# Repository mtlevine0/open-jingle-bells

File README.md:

# Open Jingle Bells

An ESP32-based replacement for the "Ye Merrie Minstrel Caroling Christmas Bells" original ROM cartridge featuring wireless synchronization.  Every unit carries the same song library, and any number of units on the same Wi-Fi network play in unison, creating a choir of christmas bells.

## Overview

This project provides open-source firmware and hardware designs to replace the original ROM cartridge in Ye Merrie Minstrel handheld bell units. Using ESP-NOW wireless communication, multiple sets of bells can be synchronized to play together in a choir.  The PCB is meant to be a direct drop-in replacement to the original ROM cartridge, no modifications of the device is required.  I reccomend a power adapter with a larger current capacity than the original 200mA to compensate for the extra power comsumption of the ESP32.

I used [OSH Park](https://oshpark.com) to manufacture the PCBs.  

## Project Structure

```
├── firmware/           # Bell-unit firmware (Arduino sketch): Wi-Fi control page, songs, UDP group sync
│   └── rom-dumper/     # Firmware for dumping ROM contents over a serial connection
├── hardware/
│   └── open-jingle-bells-module/  # KiCad project: bell-unit board
├── tools/              # Python package: song library (roms/), new songs (songs/), song and bell tools, sync monitor
└── docs/
```

## Hardware

The custom PCB is designed in KiCad and interfaces with the original bell unit via a 24-pin edge card connector, replacing the ROM cartridge.

## Demo

[View operation video](https://youtube.com/shorts/tzY3T9JohGE?feature=share)

## Firmware

### Bell unit
Each bell unit runs the Open Jingle Bells firmware. It plays its compiled-in song library by driving the 12-bit parallel data bus to the bell's solenoids. A phone sets it up and controls it through a web page, and units on the same network keep a shared clock over UDP so they play together. It also takes strikes over USB serial, for developing songs. See `firmware/README.md`.

### Rom Dumper
The original ROM contains copyrighted material.  I don't have permission to share the contents.  You can acquire your own ROM cartridge and dump the ROM using the Arduino program provided.

## Requirements

- ESP32 development boards
- Arduino IDE with ESP32 board support
- KiCad (for hardware modifications)

## License

This project is licensed under the MIT License - see the [LICENSE](LICENSE) file for details.

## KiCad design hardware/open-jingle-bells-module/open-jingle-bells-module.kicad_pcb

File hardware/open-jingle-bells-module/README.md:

# open-jingle-bells-module

ESP32-S3 receiver board that plugs onto the bell unit's card edge (J2, EDAC 395-024-559-212).

## Rev 2 (branch `choir-v2`)

### EN fix

On rev 1, R1 (10k) ran from EN to C3, and C3 went to GND. EN had no pull-up to +3.3V.
Rev 2 wires the standard Espressif RC:

- R1 10k: +3.3V to EN
- C3 1uF: EN to GND

### J2 moved to the bottom side

The socket now hangs under the board. Its slot, mounting holes and pin rows sit in the
same X/Y positions as rev 1, so the card enters from the same side. The board now sits
at a different height relative to the card, so check the enclosure stack-up.

Mounting the socket upside down turns it 180 degrees about the insertion axis. The
contact that touches card finger *n* is now socket pin **25 − n**. The schematic has been
re-pinned to match, so every net still reaches the same finger on the bell card:

| Signal | Rev 1 J2 pin | Rev 2 J2 pin |
|--------|-------------:|-------------:|
| Bell_1 / Bell_7  | 3 / 4   | 22 / 21 |
| Bell_2 / Bell_8  | 5 / 6   | 20 / 19 |
| Bell_3 / Bell_9  | 7 / 8   | 18 / 17 |
| GND / VCC        | 9 / 10  | 16 / 15 |
| Bell_4 / Bell_10 | 19 / 20 | 6 / 5   |
| Bell_5 / Bell_11 | 21 / 22 | 4 / 3   |
| Bell_6 / Bell_12 | 23 / 24 | 2 / 1   |

No firmware change is needed, because the ESP32 GPIO for each bell is unchanged.

J2 uses `card_edge_395024559212_noMH`, the rev 1 footprint without its two mounting
holes. The socket's mounting ears hang off the board edge and the socket is held by its
24 solder pins. Because the schematic symbol still has its MH1/MH2 pins (no-connect),
the parity check warns that pins 25 and 26 have no pad.

### Smaller outline

The board is 53.7–80.5 × 61–98 mm (26.8 × 37 mm), down from 35 × 55 mm in rev 1 and
26.8 × 47 mm in the first rev 2 layout. What sets the limits:

- left edge: 0.5 mm outside the copper of J2's outer pin row
- top edge: the base of the module's antenna; the antenna hangs off the board
- bottom edge: J2's lowest pins (y 94.55) and the stack of rows under U1. **J1 moved up
  10 mm with it, so the enclosure's USB-C opening has to move too.**
- right edge: the ESP32 module and USB-C

### Placement: R and C on the back

Every resistor and capacitor is on the back, behind the part it serves. The back can't
use x < 60.7 mm, because J2's socket body covers that strip.

| Back side | Behind |
|-----------|--------|
| C7, C8 (3V3 decoupling), R1, C3 (EN RC) | U1's 3V3 and EN pins, under the module |
| R2, R5 | their LEDs D2, D3 |
| R6 (GPIO0 pull-up) | S1 (BOOT) |
| C9 (VBUS) | U4 |
| R3, R4 (CC pull-downs) | J1 |
| C1, C2 (LDO in/out) | U2 |

The top side has three rows under U1:
- row A: D2, D3 and J3, with J3 now horizontal along the module's bottom edge
- row B: S2, S1 and U4
- row C, on the bottom edge: U2 and J1

The UART pin labels on the back sit just above J3's pins.

### Smaller passives

LEDs D2/D3 are now 0805 and all resistors (R1–R5) are 0603, both hand-solder variants.
Capacitors stay 0805.

### USB routing

The J1/U4/C9 corner is hand-routed and locked (`route/usb_v3.py`):
- D− (4 mm, no vias) joins B7/A7 on a bar above the pads and runs straight up to U4 pin 3.
- D+ (12 mm, 2 vias) joins A6/B6 on a bar below the pads. It drops to B.Cu, runs up
  between C9's pads and comes back to F.Cu above U4 to reach pin 1.
- A via beside U4 pin 2 ties it to C9's GND pad on the back.
- J1's left VBUS pin gets its own via.

Freerouting routed U4 to U1 (IO19/IO20): USB_D+ is 29.6 mm and USB_D− 31.0 mm, with
4 vias each and 1.4 mm skew. They aren't a coupled pair any more. That's fine at USB full
speed (12 Mb/s), where the skew is far below a bit time and impedance isn't controlled
anyway.

### Routing

The board was re-routed with Freerouting using the scripts in `route/`:

1. `v2_layout.py` takes the **rev 1** board and the rev 2 netlist. It applies pad nets,
   flips J2, places parts, and sets the outline and pour.
2. Export the DSN with `pcbnew.ExportSpecctraDSN`, then run `post_dsn.py`. This strips
   the planes, insets the boundary 0.5 mm, renames J1's hyphenated pins and sets
   0.25/0.45 mm net classes.
   Before the export, `usb_pair.py` adds the hand-routed USB tracks (locked, so they go to
   Freerouting as fixed wiring).
3. Route with Freerouting. `import_ses.py` imports the SES, drops the zero-length stubs
   Freerouting leaves on fixed nets, widens any track necked below 0.1524 mm, and fills
   the zones.
4. `gnd_cleanup_drc.py` removes redundant GND traces. It keeps a removal only when
   DRC shows no new unconnected items, starved thermals or connection-width warnings.

The routed job (`route/choir-v2.dsn`, `.ses`) is kept locally; the repo ignores `*.dsn` and `*.ses`.

The shrunk layout replaced step 1 and the USB step:

1. `v3_layout.py` strips the routing, places parts top and back, and moves the outline and
   pours to y = 98. Run it with the project's `.kicad_pro` next to the input board, or
   pcbnew loads default design rules and saves them over the project's.
2. `usb_v3.py` adds the locked J1/U4/C9 routing (see above).
3. DSN export, `post_dsn.py`, Freerouting, `import_ses.py` and `gnd_cleanup_drc.py` as
   before. Cleanup removed 77 of 83 GND segments.
4. `silk_v3.py` moves each reference label to the nearest spot clear of pads and other
   silkscreen, at the board's minimum text size (0.8 mm).

Remaining DRC items, all from before this layout apart from the last one:
- U1's 0.2 mm via drills
- U1's silkscreen at the antenna edge
- library-mismatch notes
- the U1/J2 parity notes
- one starved-thermal warning: R4's GND pad has a single spoke into the back pour

With clearance re-enabled, the only clearance hits are the 11 inside J1's own pads.

### Schematic cleanup

- R2/R5 are 1.5k so the LEDs glow dimly for debugging: about 1 mA for red/yellow,
  about 0.4 mA for blue/white/green.
- R6 (10k, 0603) pulls GPIO0 up to +3.3V. S1 stays: it selects download mode at reset
  for flashing over J3, and works as a user button (active low) after boot. Firmware
  debounces it.
- C5 and C6, the caps across the buttons, are gone. C5 was in parallel with C3, and C3
  with R1 already filters EN.
- S1/S2 are XUNPU TS-1088-AR02016 (3.9 × 3 × 2 mm SMD tactile, LCSC C720477) on KiCad's
  `Button_Switch_SMD:SW_SPST_TS-1088-xR020`, the same switch the IV-9 numitron clock
  uses. The symbol is still named `1825966-1`.
- A note on the sheet says the IO35 LED needs a module without octal PSRAM (N8). N8R8 and
  N16R8 use IO35–IO37 for PSRAM.
- ERC is clean (0 errors, 0 warnings). U1's GND pins are `power_in` and J1's are `passive`
  in the vendor libraries, and PWR_FLAGs mark VCC and GND. Two wire stubs on the
  USB_D± labels were trimmed. The Bell_9 label moved off J2's GND symbol.
- The project now has its own `sym-lib-table` and `fp-lib-table`. `footprints.pretty`
  holds J1, U2 and J2 as placed on the board, exported from the PCB. The J2 symbol was
  rebuilt into `../vendor/edac_395-024-559-212/` with the same pin positions.

### Known items carried over from rev 1

- U1's footprint has 0.2 mm thermal-via drills, below the 0.254 mm minimum in board setup
  (12 DRC errors in both revisions).
- The 3D model paths for J1, J2 and U2 point at a macOS path, so they don't render here.

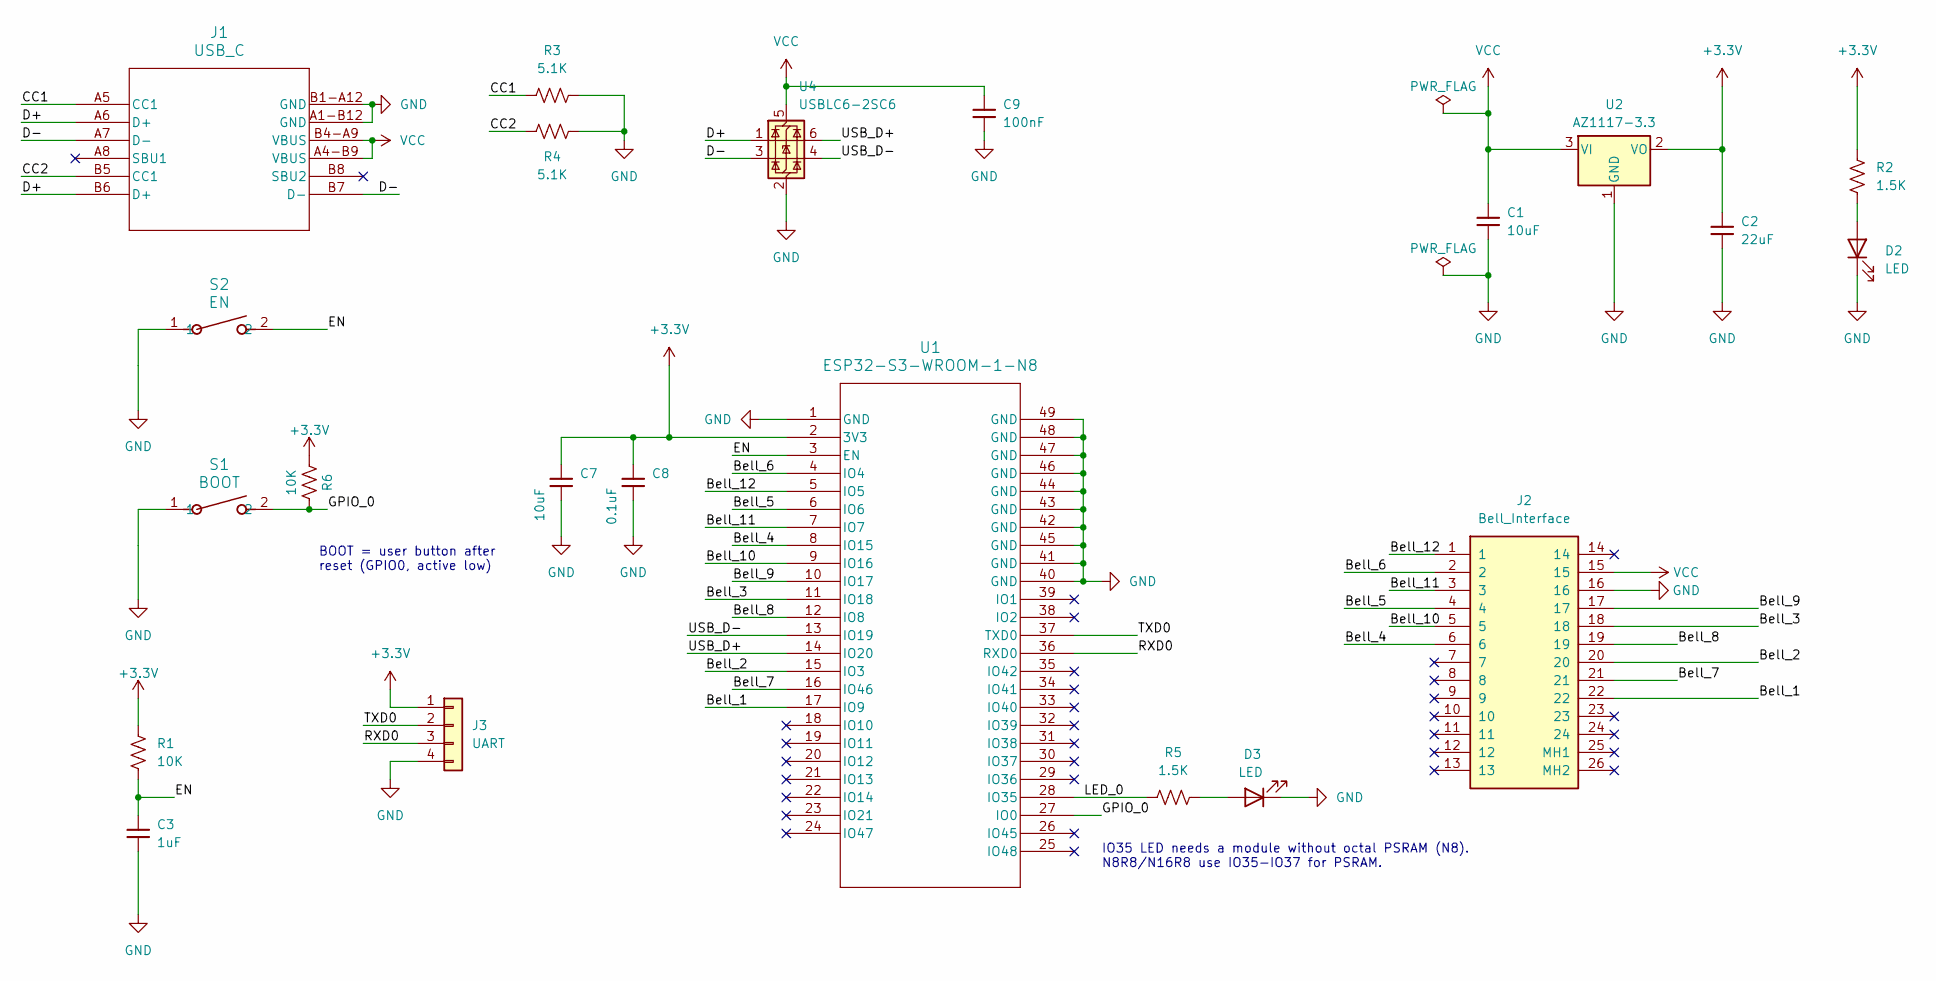
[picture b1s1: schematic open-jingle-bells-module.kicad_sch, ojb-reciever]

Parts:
C1, C7: 10uF; C_0805_2012Metric_Pad1.18x1.45mm_HandSolder
C2: 22uF; C_0805_2012Metric_Pad1.18x1.45mm_HandSolder
C3: 1uF; C_0805_2012Metric_Pad1.18x1.45mm_HandSolder
C8: 0.1uF; C_0805_2012Metric_Pad1.18x1.45mm_HandSolder
C9: 100nF; C_0805_2012Metric_Pad1.18x1.45mm_HandSolder
D2, D3: LED; LED_0805_2012Metric_Pad1.15x1.40mm_HandSolder
J1: USB_C; 12402012E212A_AMP
J2: Bell_Interface; card_edge_395024559212_noMH; Manufacturer_Part_Number 395-024-559-212
J3: UART; PinHeader_1x04_P2.54mm_Vertical
R1, R6: 10K; R_0603_1608Metric_Pad0.98x0.95mm_HandSolder
R2, R5: 1.5K; R_0603_1608Metric_Pad0.98x0.95mm_HandSolder
R3, R4: 5.1K; R_0603_1608Metric_Pad0.98x0.95mm_HandSolder
S1: BOOT; SW_SPST_TS-1088-xR020; Manufacturer_Part_Number TS-1088-AR02016
S2: EN; SW_SPST_TS-1088-xR020; Manufacturer_Part_Number TS-1088-AR02016
U1: ESP32-S3-WROOM-1-N8; ESP32-S3-WROOM-1
U2: AZ1117-3.3; SOT-223_DIO
U4: USBLC6-2SC6; SOT-23-6

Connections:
+3.3V: C2.1, C7.1, C8.1, J3.1, R1.1, R2.1, R6.1, U1.2 (3V3), U2.2 (VO)
/Bell_1: J2.22, U1.17 (IO9)
/Bell_2: J2.20, U1.15 (IO3)
/Bell_3: J2.18, U1.11 (IO18)
/Bell_4: J2.6, U1.8 (IO15)
/Bell_5: J2.4, U1.6 (IO6)
/Bell_6: J2.2, U1.4 (IO4)
/Bell_7: J2.21, U1.16 (IO46)
/Bell_8: J2.19, U1.12 (IO8)
/Bell_9: J2.17, U1.10 (IO17)
/Bell_10: J2.5, U1.9 (IO16)
/Bell_11: J2.3, U1.7 (IO7)
/Bell_12: J2.1, U1.5 (IO5)
/CC1: J1.A5 (CC1), R3.1
/CC2: J1.B5 (CC1), R4.1
/D+: J1.A6 (D+), J1.B6 (D+), U4.1 (I/O1)
/D-: J1.A7 (D-), J1.B7 (D-), U4.3 (I/O2)
/EN: C3.1, R1.2, S2.2, U1.3 (EN)
/GPIO_0: R6.2, S1.2, U1.27 (IO0)
/LED_0: R5.1, U1.28 (IO35)
/RXD0: J3.3, U1.36 (RXD0)
/TXD0: J3.2, U1.37 (TXD0)
/USB_D+: U1.14 (IO20), U4.6 (I/O1)
/USB_D-: U1.13 (IO19), U4.4 (I/O2)
GND: C1.2, C2.2, C3.2, C7.2, C8.2, C9.1, D2.1 (K), D3.1 (K), J1.A1-B12 (GND), J1.B1-A12 (GND), J2.16, J3.4, R3.2, R4.2, S1.1, S2.1, U1.1 (GND), U1.40 (GND), U1.41 (GND), U1.42 (GND), U1.43 (GND), U1.44 (GND), U1.45 (GND), U1.46 (GND), U1.47 (GND), U1.48 (GND), U1.49 (GND), U2.1 (GND), U4.2 (GND)
unnamed: D2.2 (A), R2.2
unnamed: D3.2 (A), R5.2
VCC: C1.1, C9.2, J1.A4-B9 (VBUS), J1.B4-A9 (VBUS), J2.15, U2.3 (VI), U4.5 (VBUS)

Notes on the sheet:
IO35 LED needs a module without octal PSRAM (N8). N8R8/N16R8 use IO35-IO37 for PSRAM.
BOOT = user button after reset (GPIO0, active low)

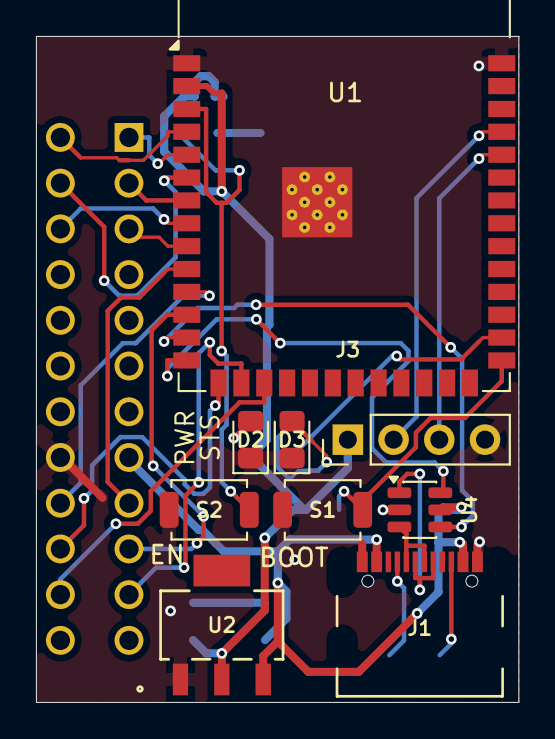
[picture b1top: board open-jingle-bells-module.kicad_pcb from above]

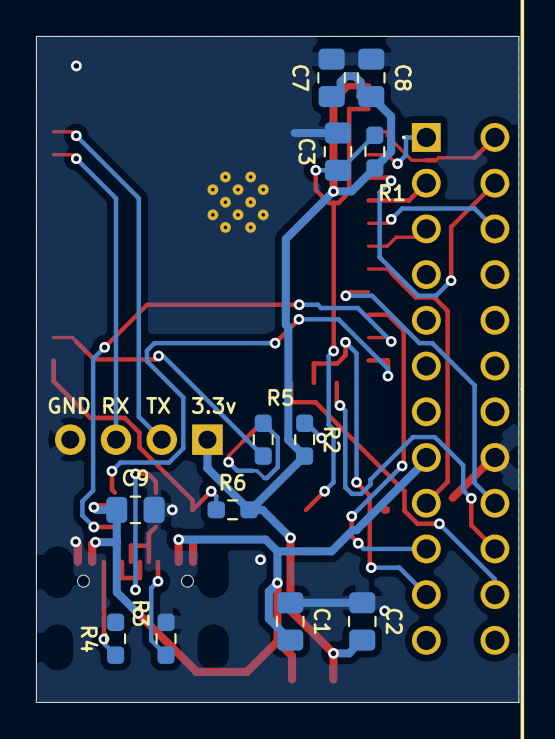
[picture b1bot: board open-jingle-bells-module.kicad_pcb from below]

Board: 2 copper layers, 26.8 x 37.0 mm, 22 parts (13 on the bottom side), 28 nets.

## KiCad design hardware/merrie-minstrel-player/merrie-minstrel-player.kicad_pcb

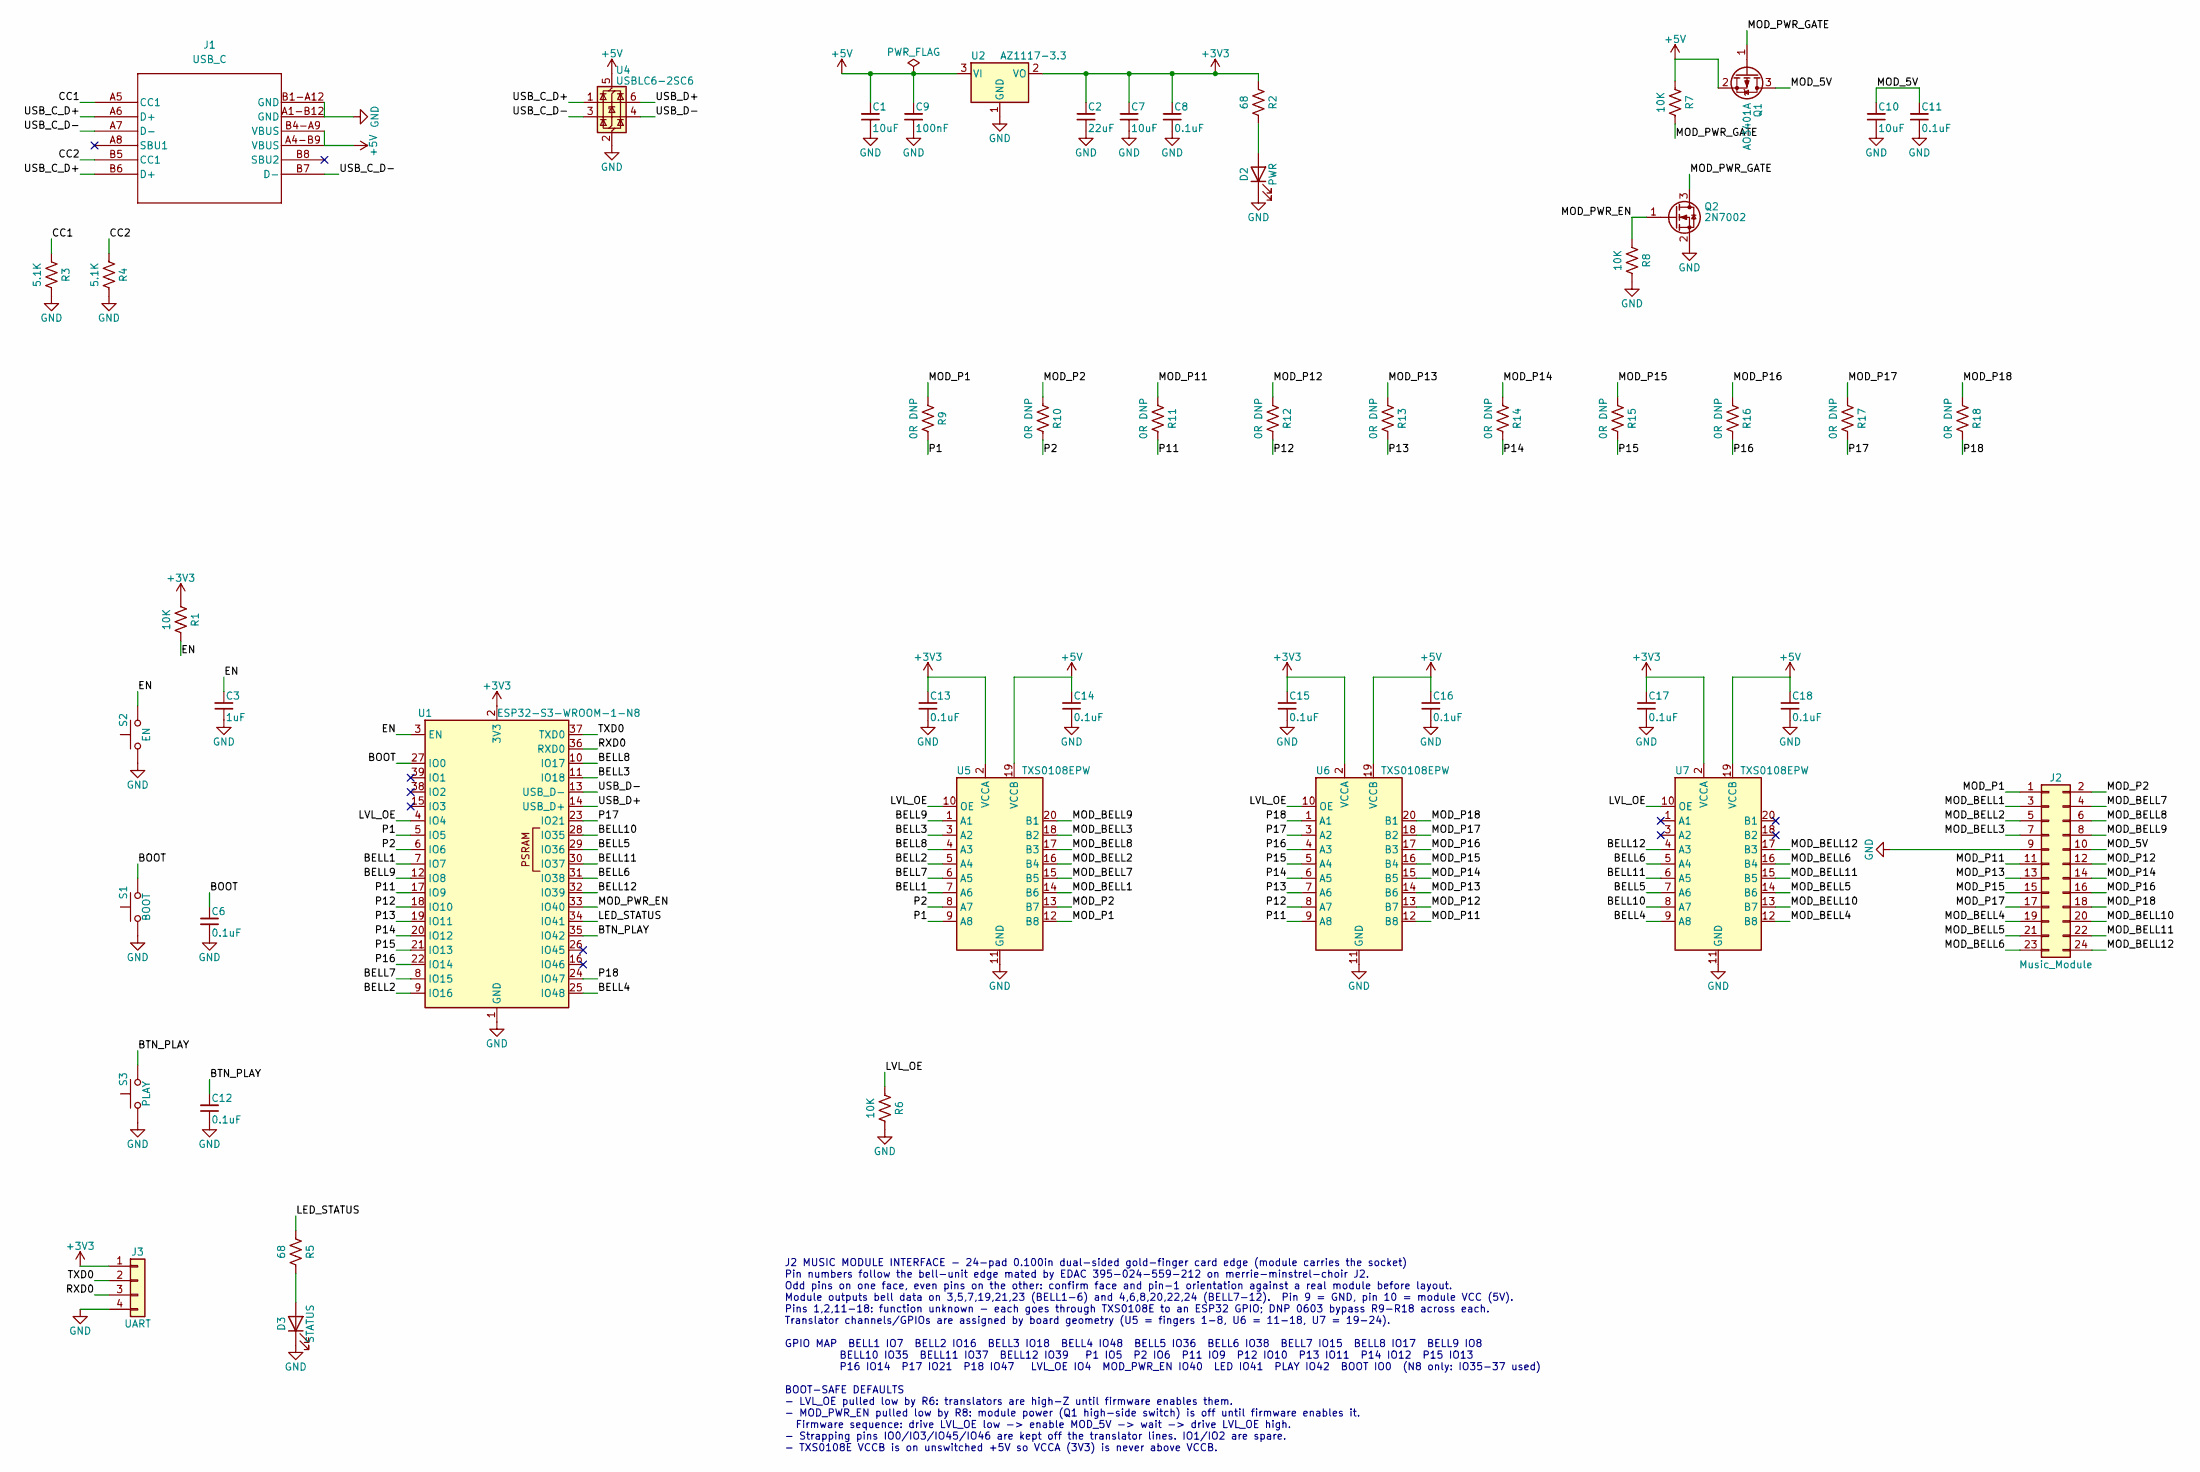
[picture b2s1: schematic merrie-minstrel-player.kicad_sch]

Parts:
C1, C7, C10: 10uF; C_0805_2012Metric_Pad1.18x1.45mm_HandSolder
C2: 22uF; C_0805_2012Metric_Pad1.18x1.45mm_HandSolder
C3: 1uF; C_0805_2012Metric_Pad1.18x1.45mm_HandSolder
C6, C8, C11, C12, C13, C14, C15, C16, C17, C18: 0.1uF; C_0805_2012Metric_Pad1.18x1.45mm_HandSolder
C9: 100nF; C_0805_2012Metric_Pad1.18x1.45mm_HandSolder
D2: PWR; LED_1206_3216Metric
D3: STATUS; LED_1206_3216Metric
J1: USB_C; 12402012E212A_AMP
J2: Music_Module; CardEdge_2x12_P2.54mm_GoldFinger
J3: UART; PinHeader_1x04_P2.54mm_Vertical
Q1: AO3401A; SOT-23
Q2: 2N7002; SOT-23
R1, R6, R7, R8: 10K; R_0805_2012Metric_Pad1.20x1.40mm_HandSolder
R2, R5: 68; R_0805_2012Metric_Pad1.20x1.40mm_HandSolder
R3, R4: 5.1K; R_0805_2012Metric_Pad1.20x1.40mm_HandSolder
R9, R10, R11, R12, R13, R14, R15, R16, R17, R18: 0R DNP; R_0603_1608Metric_Pad0.98x0.95mm_HandSolder
S1: BOOT; SW_SPST_CK_RS282G05A3
S2: EN; SW_SPST_CK_RS282G05A3
S3: PLAY; SW_SPST_CK_RS282G05A3
U1: ESP32-S3-WROOM-1-N8; ESP32-S3-WROOM-1
U2: AZ1117-3.3; SOT-223_DIO
U4: USBLC6-2SC6; SOT-23-6
U5, U6, U7: TXS0108EPW; TSSOP-20_4.4x6.5mm_P0.65mm

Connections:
+3V3: C2.1, C7.1, C8.1, C13.1, C15.1, C17.1, J3.1, R1.1, R2.1, U1.2 (3V3), U2.2 (VO), U5.2 (VCCA), U6.2 (VCCA), U7.2 (VCCA)
+5V: C1.1, C9.1, C14.1, C16.1, C18.1, J1.A4-B9 (VBUS), J1.B4-A9 (VBUS), Q1.2 (S), R7.1, U2.3 (VI), U4.5 (VBUS), U5.19 (VCCB), U6.19 (VCCB), U7.19 (VCCB)
/BELL1: U1.7 (IO7), U5.7 (A6)
/BELL2: U1.9 (IO16), U5.5 (A4)
/BELL3: U1.11 (IO18), U5.3 (A2)
/BELL4: U1.25 (IO48), U7.9 (A8)
/BELL5: U1.29 (IO36), U7.7 (A6)
/BELL6: U1.31 (IO38), U7.5 (A4)
/BELL7: U1.8 (IO15), U5.6 (A5)
/BELL8: U1.10 (IO17), U5.4 (A3)
/BELL9: U1.12 (IO8), U5.1 (A1)
/BELL10: U1.28 (IO35), U7.8 (A7)
/BELL11: U1.30 (IO37), U7.6 (A5)
/BELL12: U1.32 (IO39), U7.4 (A3)
/BOOT: C6.1, S1.2, U1.27 (IO0)
/BTN_PLAY: C12.1, S3.2, U1.35 (IO42)
/CC1: J1.A5 (CC1), R3.1
/CC2: J1.B5 (CC1), R4.1
/EN: C3.1, R1.2, S2.2, U1.3 (EN)
/LED_STATUS: R5.1, U1.34 (IO41)
/LVL_OE: R6.1, U1.4 (IO4), U5.10 (OE), U6.10 (OE), U7.10 (OE)
/MOD_5V: C10.1, C11.1, J2.10, Q1.3 (D)
/MOD_BELL1: J2.3, U5.14 (B6)
/MOD_BELL2: J2.5, U5.16 (B4)
/MOD_BELL3: J2.7, U5.18 (B2)
/MOD_BELL4: J2.19, U7.12 (B8)
/MOD_BELL5: J2.21, U7.14 (B6)
/MOD_BELL6: J2.23, U7.16 (B4)
/MOD_BELL7: J2.4, U5.15 (B5)
/MOD_BELL8: J2.6, U5.17 (B3)
/MOD_BELL9: J2.8, U5.20 (B1)
/MOD_BELL10: J2.20, U7.13 (B7)
/MOD_BELL11: J2.22, U7.15 (B5)
/MOD_BELL12: J2.24, U7.17 (B3)
/MOD_P1: J2.1, R9.1, U5.12 (B8)
/MOD_P2: J2.2, R10.1, U5.13 (B7)
/MOD_P11: J2.11, R11.1, U6.12 (B8)
/MOD_P12: J2.12, R12.1, U6.13 (B7)
/MOD_P13: J2.13, R13.1, U6.14 (B6)
/MOD_P14: J2.14, R14.1, U6.15 (B5)
/MOD_P15: J2.15, R15.1, U6.16 (B4)
/MOD_P16: J2.16, R16.1, U6.17 (B3)
/MOD_P17: J2.17, R17.1, U6.18 (B2)
/MOD_P18: J2.18, R18.1, U6.20 (B1)
/MOD_PWR_EN: Q2.1 (G), R8.1, U1.33 (IO40)
/MOD_PWR_GATE: Q1.1 (G), Q2.3 (D), R7.2
/P1: R9.2, U1.5 (IO5), U5.9 (A8)
/P2: R10.2, U1.6 (IO6), U5.8 (A7)
/P11: R11.2, U1.17 (IO9), U6.9 (A8)
/P12: R12.2, U1.18 (IO10), U6.8 (A7)
/P13: R13.2, U1.19 (IO11), U6.7 (A6)
/P14: R14.2, U1.20 (IO12), U6.6 (A5)
/P15: R15.2, U1.21 (IO13), U6.5 (A4)
/P16: R16.2, U1.22 (IO14), U6.4 (A3)
/P17: R17.2, U1.23 (IO21), U6.3 (A2)
/P18: R18.2, U1.24 (IO47), U6.1 (A1)
/RXD0: J3.3, U1.36 (RXD0)
/TXD0: J3.2, U1.37 (TXD0)
/USB_C_D+: J1.A6 (D+), J1.B6 (D+), U4.1 (I/O1)
/USB_C_D-: J1.A7 (D-), J1.B7 (D-), U4.3 (I/O2)
/USB_D+: U1.14 (USB_D+), U4.6 (I/O1)
/USB_D-: U1.13 (USB_D-), U4.4 (I/O2)
GND: C1.2, C2.2, C3.2, C6.2, C7.2, C8.2, C9.2, C10.2, C11.2, C12.2, C13.2, C14.2, C15.2, C16.2, C17.2, C18.2, D2.1 (K), D3.1 (K), J1.A1-B12 (GND), J1.B1-A12 (GND), J2.9, J3.4, Q2.2 (S), R3.2, R4.2, R6.2, R8.2, S1.1, S2.1, S3.1, U1.1 (GND), U1.40 (GND), U1.41 (GND), U2.1 (GND), U4.2 (GND), U5.11 (GND), U6.11 (GND), U7.11 (GND)
unnamed: D2.2 (A), R2.2
unnamed: D3.2 (A), R5.2

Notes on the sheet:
J2 MUSIC MODULE INTERFACE - 24-pad 0.100in dual-sided gold-finger card edge (module carries the socket) Pin numbers follow the bell-unit edge mated by EDAC 395-024-559-212 on merrie-minstrel-choir J2. Odd pins on one face, even pins on the other: confirm face and pin-1 orientation against a real mo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

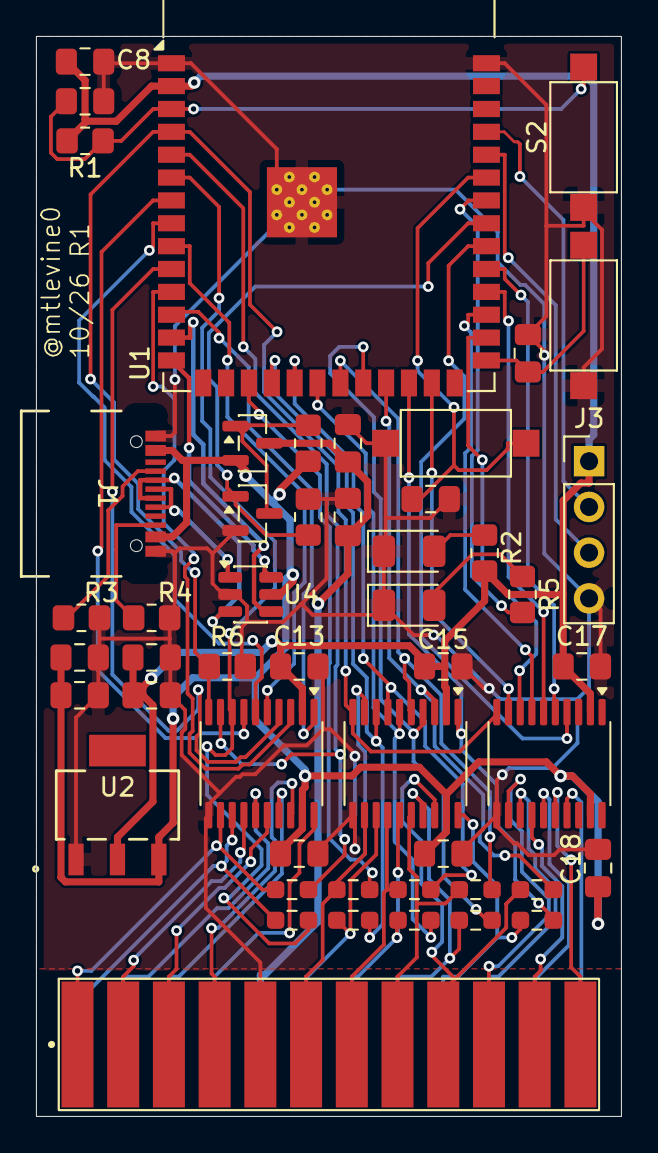
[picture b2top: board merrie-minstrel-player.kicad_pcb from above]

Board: 2 copper layers, 32.5 x 60.0 mm, 50 parts (0 on the bottom side), 65 nets.
